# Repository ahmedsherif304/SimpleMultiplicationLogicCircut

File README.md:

# SimpleMultiplicationLogicCircut
a simple multiplication circut that uses simple ICs 
it calculates in binary and show the result in binary also at most 3*3
using logism to make the IC's design and Eagle to print the board on a copper plate

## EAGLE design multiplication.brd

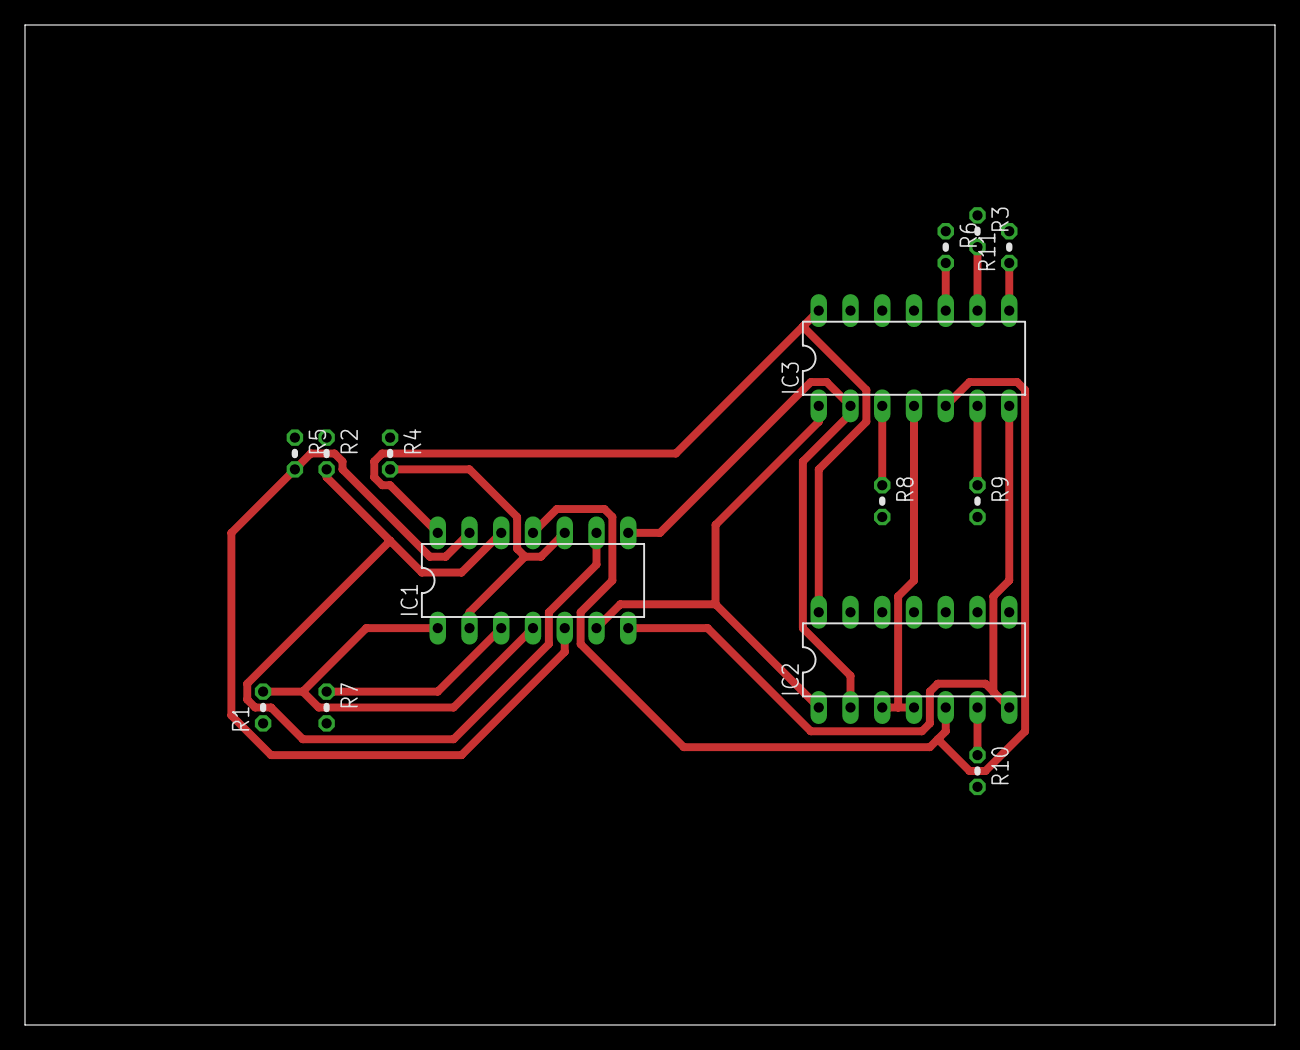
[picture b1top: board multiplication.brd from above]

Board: 2 copper layers, 100.0 x 80.0 mm, 14 parts (0 on the bottom side), 17 nets.

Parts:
IC1, IC2: 74LS08N; DIL14
IC3: 74LS86N; DIL14
R1, R2, R3, R4, R5, R6, R7, R8, R9, R10, R11: 10; 0204V

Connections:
A0: IC1.1, IC1.4, R1.2
A1: IC1.9, IC1.12, R2.2
A2: IC3.9, R3.2
B0: IC1.2, IC1.10, R4.2
B1: IC1.5, IC1.13, R5.2
B2: IC3.10, R6.2
GND: IC1.7, IC2.7, IC3.7
unnamed: IC1.3, R7.1
unnamed: IC3.8, R11.1
unnamed: IC2.6, R10.1
unnamed: IC1.6, IC2.1, IC3.1
unnamed: IC1.8, IC2.2, IC3.2
unnamed: IC3.3, R8.1
unnamed: IC2.3, IC2.4, IC3.4
unnamed: IC1.11, IC2.5, IC3.5
unnamed: IC3.6, R9.1
VCC: IC1.14, IC2.14, IC3.14

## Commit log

2019-02-02 adding the schematic and board
